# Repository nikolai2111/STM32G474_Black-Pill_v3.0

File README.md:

<!-- Improved compatibility of back to top link: See: https://github.com/othneildrew/Best-README-Template/pull/73 -->

<!--
*** Thanks for checking out the Best-README-Template. If you have a suggestion
*** that would make this better, please fork the repo and create a pull request
*** or simply open an issue with the tag "enhancement".
*** Don't forget to give the project a star!
*** Thanks again! Now go create something AMAZING! :D
-->

<!-- PROJECT SHIELDS -->
<!--
*** I'm using markdown "reference style" links for readability.
*** Reference links are enclosed in brackets [ ] instead of parentheses ( ).
*** See the bottom of this document for the declaration of the reference variables
*** for contributors-url, forks-url, etc. This is an optional, concise syntax you may use.
*** https://www.markdownguide.org/basic-syntax/#reference-style-links
-->
[![Contributors][contributors-shield]][contributors-url]
[![Forks][forks-shield]][forks-url]
[![Stargazers][stars-shield]][stars-url]
[![Issues][issues-shield]][issues-url]
[![CERN-OHL-P-2.0 License][license-shield]][license-url]

<!-- PROJECT LOGO -->
<br />
<div align="center">

<h3 align="center">Black Pill v3.0 STM32G474</h3>

  <p align="center">
    The STM32-Pills are compact and convenient for prototyping, but their digital focus leaves room for exploration. The STM32G474's integration of analog and digital components opens up possibilities for creating versatile systems. For example, the integrated opamps and comparators. 
    <br />
    <a href="https://github.com/nikolai2111/STM32G474_Black-Pill_v3.0"><strong>Explore the docs »</strong></a>
    <br />
    <br />
    <a href="https://github.com/nikolai2111/STM32G474_Black-Pill_v3.0">View Demo</a>
    ·
    <a href="https://github.com/nikolai2111/STM32G474_Black-Pill_v3.0/issues/new?labels=bug&template=bug-report---.md">Report Bug</a>
    ·
    <a href="https://github.com/nikolai2111/STM32G474_Black-Pill_v3.0/issues/new?labels=enhancement&template=feature-request---.md">Request Feature</a>
  </p>
</div>

<!-- TABLE OF CONTENTS -->
<details>
  <summary>Table of Contents</summary>
  <ol>
    <li>
      <a href="#about-the-project">About The Project</a>
      <ul>
        <li><a href="#built-with">Built With</a></li>
      </ul>
    </li>
    <li>
      <a href="#getting-started">Getting Started</a>
      <ul>
        <li><a href="#prerequisites">Prerequisites</a></li>
        <li><a href="#installation">Installation</a></li>
      </ul>
    </li>
    <li><a href="#usage">Usage</a></li>
    <li><a href="#roadmap">Roadmap</a></li>
    <li><a href="#contributing">Contributing</a></li>
    <li><a href="#license">License</a></li>
    <li><a href="#contact">Contact</a></li>
  </ol>
</details>

<!-- ABOUT THE PROJECT -->
## About The Project

[![Product Name Screen Shot][product-screenshot]](https://www.tindie.com/products/nikolai2111/black-pill-v30-stm32g474/)

I find the compact and versatile STM32-Pills (Blue and Black) intriguing due to their ease of use for various applications. They seamlessly integrate into hardware prototypes, simplifying the process of testing ideas. However, I’ve noticed that the existing Black Pills primarily focus on digital tasks.

On the other hand, the STM32G474 stands out as a fascinating microcontroller that bridges the gap between the digital and analog worlds. What piques my interest are its integrated analog components, such as op-amps and comparators, coupled with digital interfaces. This combination offers an exciting opportunity to develop systems that seamlessly blend both digital and analog functionalities.

In summary, while the compact and convenient Pills are fascinating tools for rapid prototyping, their current digital focus leaves room for exploration. In contrast, the STM32G474’s integration of analog and digital components opens up exciting possibilities for creating versatile, boundary-pushing systems.

<p align="right">(<a href="#readme-top">back to top</a>)</p>

### Built With

* [][Kicad-url]

<p align="right">(<a href="#readme-top">back to top</a>)</p>

<!-- GETTING STARTED -->
## Getting Started

### Prerequisites

Install KiCad 8.0 on your computer.

### Installation

ToDo:
1. Clone the repo to your STM32CubeIDE workspace
   ```sh
   git clone https://github.com/nikolai2111/STM32G474_Black-Pill_v3.0.git
   ```
2. Navigate to the the `src` folder.
3. Open the [project file](src/STM32G474_Black-Pill_v3.0.kicad_pro).

<p align="right">(<a href="#readme-top">back to top</a>)</p>

<!-- USAGE EXAMPLES -->
## Usage

Use this dev board with the template from [this repo](https://github.com/nikolai2111/STM32G474_Black-Pill_v3.0_Template). It's an example file.

<p align="right">(<a href="#readme-top">back to top</a>)</p>

<!-- ROADMAP -->
## Roadmap

- [ ] SW: Publish HAL template for this board.
- [ ] SW: Add LL template for this board.

See the [open issues](https://github.com/nikolai2111/STM32G474_Black-Pill_v3.0/issues) for a full list of proposed features (and known issues).

<p align="right">(<a href="#readme-top">back to top</a>)</p>

<!-- CONTRIBUTING -->
## Contributing

Contributions are what make the open source community such an amazing place to learn, inspire, and create. Any contributions you make are **greatly appreciated**.

If you have a suggestion that would make this better, please fork the repo and create a pull request. You can also simply open an issue with the tag "enhancement".
Don't forget to give the project a star! Thanks again!

1. Fork the Project
2. Create your Feature Branch (`git checkout -b feature/AmazingFeature`)
3. Commit your Changes (`git commit -m 'Add some AmazingFeature'`)
4. Push to the Branch (`git push origin feature/AmazingFeature`)
5. Open a Pull Request

<p align="right">(<a href="#readme-top">back to top</a>)</p>

<!-- LICENSE -->
## License

Distributed under the CERN-OHL-P-2.0 License. See `LICENSE.txt` for more information.

<p align="right">(<a href="#readme-top">back to top</a>)</p>

<!-- CONTACT -->
## Contact

Nikolai Zoller - nikolai.zoller@hotmail.com

Project Link: [https://github.com/nikolai2111/STM32G474_Black-Pill_v3.0](https://github.com/nikolai2111/STM32G474_Black-Pill_v3.0)

<p align="right">(<a href="#readme-top">back to top</a>)</p>

---
Source: [Best-README-Template](https://github.com/othneildrew/Best-README-Template)

<!-- MARKDOWN LINKS & IMAGES -->
<!-- https://www.markdownguide.org/basic-syntax/#reference-style-links -->
[contributors-shield]: https://img.shields.io/github/contributors/nikolai2111/STM32G474_Black-Pill_v3.0.svg?style=for-the-badge
[contributors-url]: https://github.com/nikolai2111/STM32G474_Black-Pill_v3.0/graphs/contributors
[forks-shield]: https://img.shields.io/github/forks/nikolai2111/STM32G474_Black-Pill_v3.0.svg?style=for-the-badge
[forks-url]: https://github.com/nikolai2111/STM32G474_Black-Pill_v3.0/network/members
[stars-shield]: https://img.shields.io/github/stars/nikolai2111/STM32G474_Black-Pill_v3.0.svg?style=for-the-badge
[stars-url]: https://github.com/nikolai2111/STM32G474_Black-Pill_v3.0/stargazers
[issues-shield]: https://img.shields.io/github/issues/nikolai2111/STM32G474_Black-Pill_v3.0.svg?style=for-the-badge
[issues-url]: https://github.com/nikolai2111/STM32G474_Black-Pill_v3.0/issues
[license-shield]: https://img.shields.io/github/license/nikolai2111/STM32G474_Black-Pill_v3.0.svg?style=for-the-badge
[license-url]: https://github.com/nikolai2111/STM32G474_Black-Pill_v3.0/blob/master/LICENSE.txt
[product-screenshot]: PCB-3D_Top_A.png
[Kicad-url]: https://www.kicad.org/

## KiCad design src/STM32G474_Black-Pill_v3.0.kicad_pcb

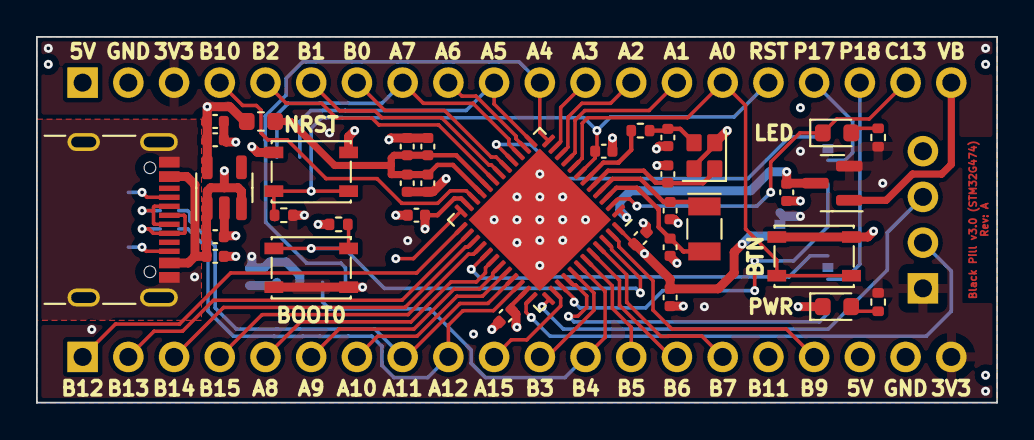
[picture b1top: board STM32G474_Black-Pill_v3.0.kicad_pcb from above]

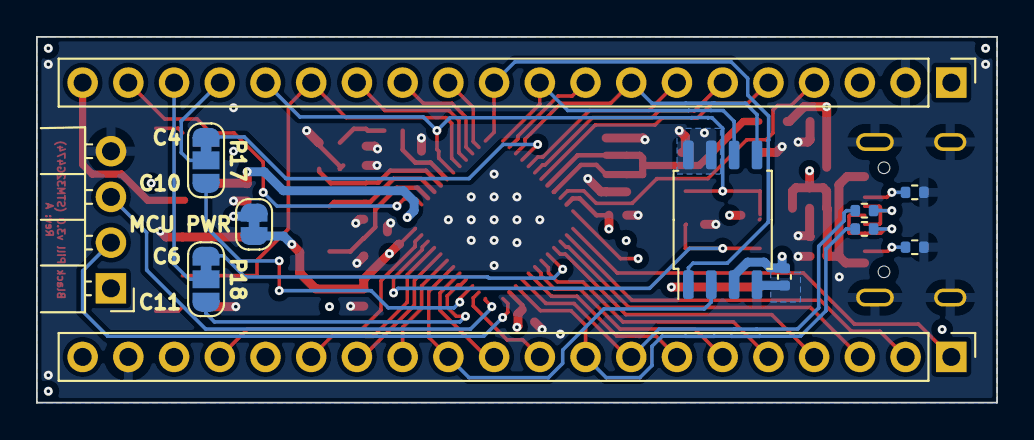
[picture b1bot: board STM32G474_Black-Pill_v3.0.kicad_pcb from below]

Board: 4 copper layers, 53.3 x 20.3 mm, 47 parts (12 on the bottom side), 58 nets.

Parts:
C101, C104, C108, C109, C110, C112, C114, C115, C119, C120: 100nF; C_0402_1005Metric
C102, C103, C105, C106: 6pF; C_0402_1005Metric
C107: 10µF; C_0402_1005Metric
C113, C116, C117, C118: 1µF; C_0402_1005Metric
D101: red; LED_0603_1608Metric
D102: BAT54C; SOT-23
D103: green; LED_0603_1608Metric
J101: USB_C_Receptacle_USB2.0; USB_C_Receptacle_GCT_USB4105-xx-A_16P_TopMnt_Horizontal
J102, J103: Conn_01x20; PinHeader_1x20_P2.54mm_Vertical
J104: Conn_01x04; PinHeader_1x04_P2.54mm_Horizontal_Board_Edge
JP101, JP102: SolderJumper_3_Bridged12; SolderJumper-3_P1.3mm_Bridged12_RoundedPad1.0x1.5mm_NumberL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
JP103: SolderJumper_2_Bridged; SolderJumper-2_P1.3mm_Bridged_RoundedPad1.0x1.5mm
L101: 10µH; L_0603_1608Metric
R101, R102: 5.1k; R_0402_1005Metric
R103, R108: 10k; R_0402_1005Metric
R104, R105: 10R; R_0402_1005Metric
R106: 0R; R_0402_1005Metric
R107, R109: 100R; R_0402_1005Metric
SW101, SW102, SW103: SW_Push; SW_SPST_PTS810
U101: W25Q32JVSS; SOIC-8_5.23x5.23mm_P1.27mm
U102: STM32G474CEUx; QFN-48-1EP_7x7mm_P0.5mm_EP5.6x5.6mm
U103: AP7343xx; SOT-23-5
Y101: 24MHz; Crystal_SMD_SeikoEpson_FA128-4Pin_2.0x1.6mm
Y102: 32.768kHz; Crystal_SMD_MicroCrystal_CC7V-T1A-2Pin_3.2x1.5mm

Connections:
+3.3V: C101.1, C115.1, C116.1, D102.2, J102.20, J103.3, J104.1, JP103.2 (B), L101.1, R103.1, R107.1, R109.1, SW102.2, U101.3 (IO2), U101.7 (IO3), U101.8 (VCC), U103.5 (OUT)
+5V: C113.1, C114.1, J101.A4 (VBUS), J101.A9 (VBUS), J101.B4 (VBUS), J101.B9 (VBUS), J102.18, J103.1, U103.1 (IN), U103.3 (EN)
/+3.3V_{MCU}: C107.1, C108.1, C109.1, C110.1, JP103.1 (A), U102.23 (VDD), U102.35 (VDD), U102.48 (VDD)
/PA0: J103.15, SW103.2, U102.8 (PA0)
/PA1: J103.14, U102.9 (PA1)
/PA2: J103.13, U102.10 (PA2)
/PA3: J103.12, U102.11 (PA3)
/PA4: J103.11, U101.1 (~CS), U102.12 (PA4)
/PA5: J103.10, U101.6 (CLK), U102.13 (PA5)
/PA6: J103.9, U102.14 (PA6)
/PA7: J103.8, U101.5 (DI(IO0)), U102.15 (PA7)
/PA8: J102.5, U102.30 (PA8)
/PA9: J102.6, U102.31 (PA9)
/PA10: J102.7, U102.32 (PA10)
/PA11: J102.8, R104.2, U102.33 (PA11)
/PA12: J102.9, R105.2, U102.34 (PA12)
/PA15: J102.10, U102.38 (PA15)
/PB0: J103.7, U102.17 (PB0)
/PB1: J103.6, U102.18 (PB1)
/PB2: J103.5, U102.19 (PB2)
/PB3: J102.11, U102.41 (PB3)
/PB4: J102.12, U101.2 (DO(IO1)), U102.42 (PB4)
/PB5: J102.13, U102.43 (PB5)
/PB6: J102.14, U102.44 (PB6)
/PB7: J102.15, U102.45 (PB7)
/PB8: R108.1, SW102.1, U102.46 (PB8)
/PB9: J102.17, U102.47 (PB9)
/PB10: J103.4, U102.22 (PB10)
/PB11: J102.16, U102.24 (PB11)
/PB12: J102.1, U102.25 (PB12)
/PB13: J102.2, U102.26 (PB13)
/PB14: J102.3, U102.27 (PB14)
/PB15: J102.4, U102.28 (PB15)
/PC4: JP101.1 (A), U102.16 (PC4)
/PC6: JP102.1 (A), U102.29 (PC6)
/PC10: JP101.3 (B), U102.39 (PC10)
/PC11: JP102.3 (B), U102.40 (PC11)
/PC13: D103.1 (K), J103.19, U102.2 (PC13)
/PC14: C105.2, U102.3 (PC14), Y102.2
/PC15: C106.2, U102.4 (PC15), Y102.1
/Pin17: J103.17, JP101.2 (C)
/Pin18: J103.18, JP102.2 (C)
/SWCLK: J104.3, U102.37 (PA14)
/SWDIO: J104.2, U102.36 (PA13)
GND: C101.2, C102.1, C103.1, C104.2, C105.1, C106.1, C107.2, C108.2, C109.2, C110.2, C112.2, C113.2, C114.2, C115.2, C116.2, C117.1, C118.1, C119.1, C120.1, D101.1 (K), J101.A1 (GND), J101.A12 (GND), J101.B1 (GND), J101.B12 (GND), J101.S1 (SHIELD), J102.19, J103.2, J104.4, R101.2, R102.2, R108.2, SW101.1, SW103.1, U101.4 (GND), U102.49 (VSS), U103.2 (GND), Y101.2, Y101.4
NRST: C104.1, J103.16, R103.2, SW101.2, U102.7 (PG10)
unnamed: C103.2, R106.2, Y101.3
unnamed: D101.2 (A), R107.2
unnamed: D103.2 (A), R109.2
unnamed: J101.A5 (CC1), R101.1
unnamed: J101.B5 (CC2), R102.1
unnamed: J101.A6 (D+), J101.B6 (D+), R105.1
unnamed: J101.A7 (D-), J101.B7 (D-), R104.1
unnamed: C102.2, U102.5 (PF0), Y101.1
unnamed: R106.1, U102.6 (PF1)
VB: D102.1, J103.20
VBAT: C112.1, D102.3, U102.1 (VBAT)
VDDA: C117.2, C118.2, C119.2, C120.2, L101.2, U102.20 (VREF+), U102.21 (VDDA)

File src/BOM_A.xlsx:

Reference | Value | Footprint | Datasheet | Manufacturer Part no. | Vendor | Vendor Part No. | Qty
C101, C104, C108-C110, C112, C114, C115, C119, C120 | 100nF | Capacitor_SMD:C_0402_1005Metric | ~ | GRM155R71C104KA88D | Digikey | 490-3261-1-ND | 10
C102, C103, C105, C106 | 6pF | Capacitor_SMD:C_0402_1005Metric | ~ | GRM1555C1H6R0BA01D | Digikey | 490-8221-1-ND | 4
C107 | 10µF | Capacitor_SMD:C_0402_1005Metric | ~ | GRM155R60J106ME15D | Digikey | 490-13238-1-ND | 1
C113, C116-C118 | 1µF | Capacitor_SMD:C_0402_1005Metric | ~ | GRM155C81C105KE11D | Digikey | 490-12700-1-ND | 4
D101 | red | LED_SMD:LED_0603_1608Metric | ~ | LTST-C190KRKT | Digikey | 160-1436-1-ND | 1
D102 | BAT54C | Package_TO_SOT_SMD:SOT-23 | http://www.diodes.com/_files/datasheets/ds11005.pdf | BAT54C | Digikey | 4878-BAT54CCT-ND | 1
D103 | green | LED_SMD:LED_0603_1608Metric | ~ | LTST-C190KGKT | Digikey | 160-1435-1-ND | 1
J101 | USB_C_Receptacle_USB2.0 | Connector_USB:USB_C_Receptacle_GCT_USB4105-xx-A_16P_TopMnt_Horizontal | https://www.usb.org/sites/default/files/documents/usb_type-c.zip | USB4105-GF-A | Digikey | 2073-USB4105-GF-ACT-ND | 1
J102, J103 | Conn_01x20 | Connector_PinHeader_2.54mm:PinHeader_1x20_P2.54mm_Vertical | ~ | - | From stock | - | 2
J104 | Conn_01x04 | Connector_PinHeader_2.54mm_User:PinHeader_1x04_P2.54mm_Horizontal_Board_Edge | ~ | - | From stock | - | 1
JP101, JP102 | SolderJumper_3_Bridged12 | Jumper:SolderJumper-3_P1.3mm_Bridged12_RoundedPad1.0x1.5mm_NumberLabels | ~ | - | - | - | 2
JP103 | SolderJumper_2_Bridged | Jumper:SolderJumper-2_P1.3mm_Bridged_RoundedPad1.0x1.5mm | ~ | - | - | - | 1
L101 | 10µH | Inductor_SMD:L_0603_1608Metric | ~ | MLZ1608M100WT000 | Digikey | 445-6389-1-ND | 1
R101, R102 | 5.1k | Resistor_SMD:R_0402_1005Metric | ~ | RC0402FR-075K1L | Digikey | 311-5.10KLRCT-ND | 2
R103, R108 | 10k | Resistor_SMD:R_0402_1005Metric | ~ | RC0402FR-0710KL | Digikey | 311-10.0KLRCT-ND | 2
R104, R105 | 10R | Resistor_SMD:R_0402_1005Metric | ~ | RC0402FR-0710RL | Digikey | 311-10.0LRCT-ND | 2
R106 | 0R | Resistor_SMD:R_0402_1005Metric | ~ | RC0402FR-070RL | Digikey | 311-0.0LRCT-ND | 1
R107, R109 | 100R | Resistor_SMD:R_0402_1005Metric | ~ | RC0402FR-07100RL | Digikey | 311-100LRCT-ND | 2
SW101-SW103 | SW_Push | Button_Switch_SMD:SW_SPST_PTS810 | ~ | PTS810 SJK 250 SMTR LFS | Digikey | CKN10503CT-ND | 3
U101 | W25Q32JVSS | Package_SO:SOIC-8_5.23x5.23mm_P1.27mm | http://www.winbond.com/resource-files/w25q32jv%20revg%200327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 | W25Q32JVSSIQ | Digikey | W25Q32JVSSIQ-ND | 1
U102 | STM32G474CEUx | Package_DFN_QFN:QFN-48-1EP_7x7mm_P0.5mm_EP5.6x5.6mm | https://www.st.com/resource/en/datasheet/stm32g474ce.pdf | STM32G474CEU6 | Digikey | 497-STM32G474CEU6-ND | 1
U103 | AP7343xx | Package_TO_SOT_SMD:SOT-23-5 | https://www.diodes.com/assets/Datasheets/AP7343.pdf | AP7343-33W5-7 | Digikey | AP7343-33W5-7DICT-ND | 1
Y101 | 24MHz | Crystal:Crystal_SMD_SeikoEpson_FA128-4Pin_2.0x1.6mm | ~ | NX2016SA-24MHZ-EXS00A-CS10820 | Digikey | 644-1365-1-ND | 1
Y102 | 32.768kHz | Crystal:Crystal_SMD_MicroCrystal_CC7V-T1A-2Pin_3.2x1.5mm | ~ | NX3215SA-32.768KHZ-EXS00A-MU00525 | Digikey | 644-1386-1-ND | 1

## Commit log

2023-10-23 Add: LICENSE
2023-10-23 Add: KiCad template to the project
2023-10-23 Add: Schematic to the project. Also added some documents.
2023-10-23 Mod: Renamed dok folder to doc
2023-10-23 Add: Files to new folder
2023-10-24 Mod: Schematic, added manufacturer no. and vendor no.
2023-10-24 Add: PCB Layout and modified schematic to suit the PCB needs
2023-10-24 Add: Exported PDFs
2023-11-12 Mod: STM32G474_Black-Pill_v3.0.kicad_sch, changed alignment of the PA1 label.
2023-11-12 Mod: STM32G474_Black-Pill_v3.0.kicad_pcb, changed footprint of STM32G474 and the whole PCB has to be adjusted.
2023-11-13 Mod: PCB and Schematic, re-exported all files.
2023-11-13 Add: Production data
2023-11-13 Add: JLCPCB Database
2023-11-28 Mod: Moved U102 on the PCB to the programming headers. Re-exported all the files.
2023-11-28 Mod: gitignore files, added zipped gerber files.
2023-11-28 Mod: STM32G474_Black-Pill_v3.0.kicad_sch, updated BOM and re-exported BOM_A.xlsx.
2023-11-28 Fix: Issue with to small annular ring.
2023-12-14 Mod: Schematic_A.pdf, renamed VREF to VDDA
2023-12-14 Mod: Moved BOM_A.xlsx to source and exported BOM_A.pdf to the repo root folder.
2023-12-14 Mod: Added excluded error markers to project.
2024-01-27 Mod: Ignored gerbers directory and added the whole finished ZIP
2024-01-27 Add: STM32G474_Black-Pill_v3.0_panel.kicad_pcb, this is a generated panel with 2x5 pcs.
2024-02-07 Mod: Renamed zip files
2024-04-28 Mod: README.md and renamed LICENSE.txt file
2024-04-28 Fix: README.md, corrected license
2024-04-28 Add: Picture to README.md
2024-04-28 Add: Tindie badge to README.md
2024-04-28 Mod: Tindie line in README.md
2024-04-28 Add: Usage chapter to README.md
2024-04-28 Mod: Name in README.md
2024-04-28 Fix: Wrong image text in README.md
